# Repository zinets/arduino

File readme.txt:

xmas_lights_multisegment - папка с исходным проектом елочной гирлянды на 5 веток (если получится, добавлю 2-3 ветки к 2020 НГ)

5 веток, подключены к D2 - D6, по 17 led в ветке

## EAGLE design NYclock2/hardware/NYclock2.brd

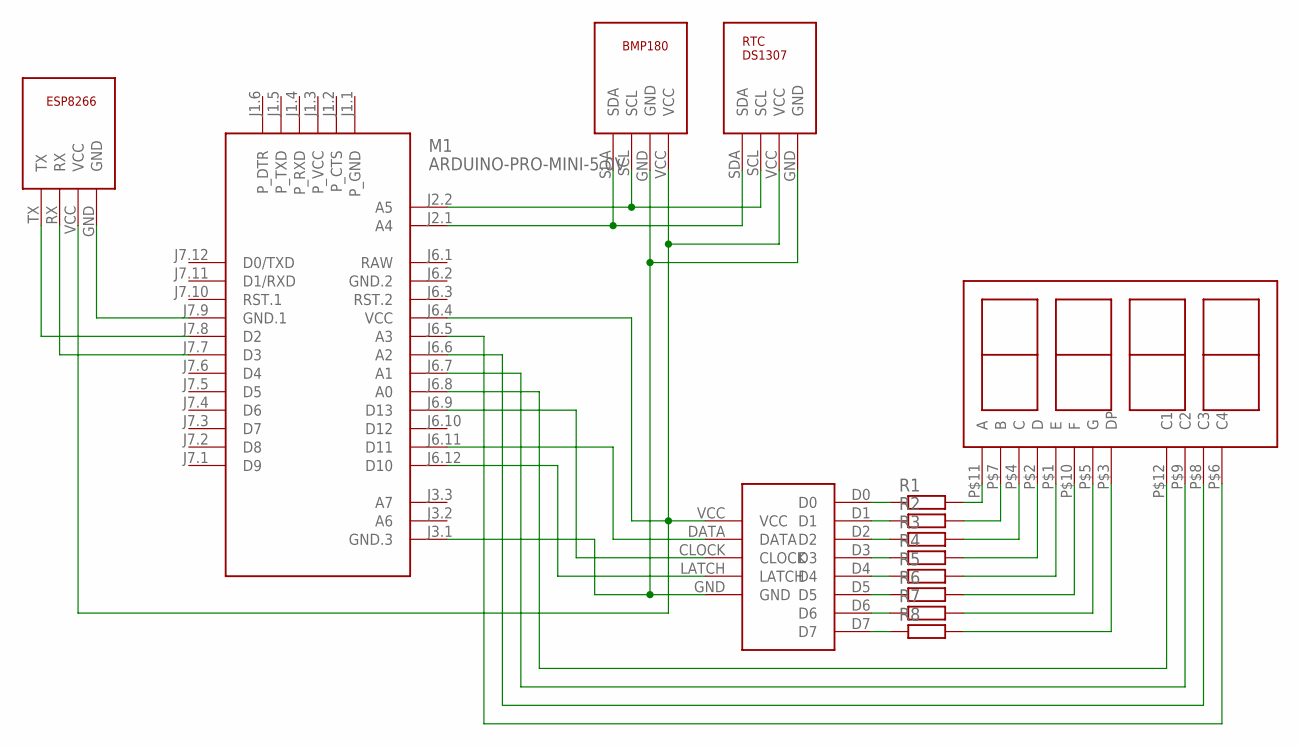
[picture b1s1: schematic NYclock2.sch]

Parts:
1: SHIFTREG
M1: ARDUINO-PRO-MINI-5.0V; ARDUINO-PRO-MINI
R1, R2, R3, R4, R5, R6, R7, R8: R-EU_0204/2V; 0204V
U$1: BMP180
U$2: 7SEGDIGITS
U$3: ESP8266
U$4: RTC

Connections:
GND.2: M1.J6.2 (GND.2)
unnamed: 1.GND, M1.J3.1 (GND.3), U$1.GND, U$4.GND
unnamed: 1.VCC, M1.J6.4 (VCC), U$1.VCC, U$3.VCC, U$4.VCC
unnamed: M1.J7.8 (D2), U$3.TX
unnamed: M1.J7.7 (D3), U$3.RX
unnamed: 1.DATA, M1.J6.11 (D11)
unnamed: 1.CLOCK, M1.J6.9 (D13)
unnamed: 1.LATCH, M1.J6.12 (D10)
unnamed: 1.D0, R1.1
unnamed: 1.D1, R2.1
unnamed: 1.D2, R3.1
unnamed: 1.D3, R4.1
unnamed: 1.D4, R5.1
unnamed: 1.D5, R6.1
unnamed: 1.D6, R7.1
unnamed: 1.D7, R8.1
unnamed: R1.2, U$2.P$11 (A)
unnamed: R2.2, U$2.P$7 (B)
unnamed: R3.2, U$2.P$4 (C)
unnamed: R4.2, U$2.P$2 (D)
unnamed: R5.2, U$2.P$1 (E)
unnamed: R6.2, U$2.P$10 (F)
unnamed: R7.2, U$2.P$5 (G)
unnamed: R8.2, U$2.P$3 (DP)
unnamed: M1.J6.5 (A3), U$2.P$6 (C4)
unnamed: M1.J6.6 (A2), U$2.P$8 (C3)
unnamed: M1.J6.7 (A1), U$2.P$9 (C2)
unnamed: M1.J6.8 (A0), U$2.P$12 (C1)
unnamed: M1.J2.2 (A5), U$1.SCL, U$4.SCL
unnamed: M1.J2.1 (A4), U$1.SDA, U$4.SDA
unnamed: M1.J7.9 (GND.1), U$3.GND
RAW: M1.J6.1 (RAW)

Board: 2 copper layers, 14 parts (0 on the bottom side), 30 nets, no tracks yet.

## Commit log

2015-01-13 ++ NYclock initial commit
2015-10-16 ++ html
2015-12-14 ++ initial commit
2015-12-14 ++ bt-controller car project
2015-12-14 ++ initial commit for first (?) version
2015-12-14 ++ initial commit for last version
2015-12-14 ++ тестовый проект в fritzing
2015-12-14 ++ .ino file was added to project
2015-12-18 ++ схема ++ инициальная прошивка
2015-12-18 ++ прошивка на 3 кнопки и зашитый пароль 01210
2015-12-20 ++ начальная усановка свеодиодов
2015-12-20 ++ 2 modes
2015-12-22 ++ tune
2015-12-28 ++ remote control
2016-03-29 ++ empty master
2016-03-29 ++ initial commit - запрос json и получение базовых цифр, проект для esp8266
2016-04-03 ++ creating new project
2016-04-03 ++ design of 1st screen)
2016-04-03 ++ waiting state
2016-04-03 ++ parsing current temp
2016-04-03 ++ filling screen 'current condition'
2016-04-03 ++ forecast screen
2016-04-03 ++ svg
2016-04-23 ++ test sketch with dht11 & ds1307
2016-12-25 ++ leds count ++ 2 palettes only
2017-02-04 ++ подключение rtc, вывод времени на lcd
2017-02-22 ++ storing last time in eeprom
2017-03-20 ++ режим отображение времени окончания
2017-03-20 ++ зачатки обновления времени по посл. порту
2017-03-20 ++ pulse dots
2017-03-21 ++ значек обеда
2017-06-27 ++ бардак-шоу #1
2017-06-27 ++ бардак-шоу #2
2017-06-27 ++ ну нихера не работает все равно
2017-10-30 ++ 1820 temp sensor
2017-11-21 ++ temp displaying
2018-08-27 ++ gps
2018-08-27 ++ need first test
2018-09-08 ++ other oled driver
2018-09-08 ++ connect gps, read from gps, output to oled
2018-09-08 ++ more classes
2018-09-09 ++ buzzer
2018-09-09 ++ works??
2018-09-21 ++ hardware sketch
2018-10-27 ++ multi boards config
2018-10-27 ++ debug
2018-10-27 ++ fix for oled display initialization
2018-10-27 ++ работающий экран и пищалка
2018-10-29 ++ try to use hardware serial with arduino
2018-11-03 ++ hardware connection to gps + debug from uart
2018-11-03 ++ шаманьство
2018-11-12 ++ новый таргет - esp8266
2018-11-12 ++ related libs
2018-11-12 ++ константы и зависимости железа в отдельные файлы для краткости
2018-11-13 ++ ready for initial testing
2018-11-13 ++ lcd moved
2018-11-13 ++ try new project, based on old one
2018-11-14 ++ new fork for "work_timer"
2018-11-14 ++ 2 шага - lcd и led
2018-11-14 ++ lib
2018-11-14 ++ button
2018-11-14 ++ rtc
2018-11-14 ++ rtc + interrupt
2018-11-15 ++ upload params
2018-11-15 ++ показ основного режима работы
2018-11-15 ++ мигалка светодиодом
2018-11-15 ++ solid palette for work mode ++ eeprom storing
2018-11-22 ++ wifi
2018-11-22 ++ time updating
2018-11-22 no message
2018-11-27 ++ schematic
2018-11-27 ++ blynk integration
2018-12-04 ++ ready for 1st test
2018-12-04 ++ теста еще не было, а уже рефактор
2018-12-04 ++ теперь - со вкусом лимона!
2019-01-02 ++ кривой обход неработающих часов
2019-01-02 ++ это уже полняй бред..
2019-01-12 ++ initial commit, "balcony" sensor
2019-01-12 ++ wifi config
2019-01-12 ++ sending measured values
2019-01-12 ++ deep sleep for energy efficient
2019-01-17 ++ bme sensor
2019-02-03 ++ new target
2019-02-03 ++ syncing data
2019-02-03 ++ tft connection
2019-02-03 ++ test for int temperature reading & displaying
2019-02-08 ++ странно, но запись в еепром заработала с использованием адреса для записи 0
2019-11-01 ++ new test project
2019-11-10 ++ base module/screen block testing
2019-11-10 ++ dummy screen test
2019-11-10 ++ short version
2019-11-10 ++ OUTPUT DIGITS
2019-12-08 нахер весь мусор, пытаюсь навести порядок с гирляндами
2019-12-08 ++ project created
2019-12-08 ++ ingor file
2019-12-08 ++ wrong arduino type - should be "arduino nano", NO "new"!
2019-12-08 ++ test for 5 branches
2019-12-08 ++ нормально работающий восстановленный вариант
2019-12-08 ++ docs updated
2019-12-08 ++ 6я ветка
2019-12-11 ++ 2 stipes test
2019-12-11 ++ orange pulsing
2019-12-25 ++ added target esp8266 + OTA
2020-01-12 ++ before experiments
2020-01-12 ++ web interface
2020-01-12 ++ управление яркостью
2021-11-04 ++ тесты с цифрами
2021-11-04 ++ reструктуризация
2021-11-04 ++ настройка таргета
2021-11-04 ++ подключение часов
2021-11-04 ++ tests...
2021-11-04 ++ working
2021-11-05 ++ wifi connection
2021-11-05 ++ ntp client
2021-11-05 ++ обновление времени
2021-11-05 ++ interrupt-driven clock
2021-11-05 ++ все цифры + пульсация
2021-11-13 ++ startup sequence
2021-11-21 ++ initial commit, hardware connection
2021-11-21 ++ dht11 sensor (unsucc)
2021-11-25 ++ похоже проблемы были из-за соединений
2021-11-25 ++ design!
2022-02-07 ++ working proto (soft reset dont)
2022-02-10 ++ в слое "1" кнопки для отладки: "-" == F8 (шаг), "+" == F7 (войти в подпрограмму), "enter" == F9 (продолжить)
2022-06-24 ++ final version
2022-06-24 ++ глючит
2022-07-11 ++ no noise
2022-07-12 ++ turning off by click
2022-09-08 ++ pinout
2022-09-08 ++ primitives
2022-09-08 ++ testing
2022-09-08 ++ working proto

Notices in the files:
parts and their libraries:
diy-modules: Released under the Creative Commons Attribution 4.0 International License: http://creativecommons.org/licenses/by/4.0
